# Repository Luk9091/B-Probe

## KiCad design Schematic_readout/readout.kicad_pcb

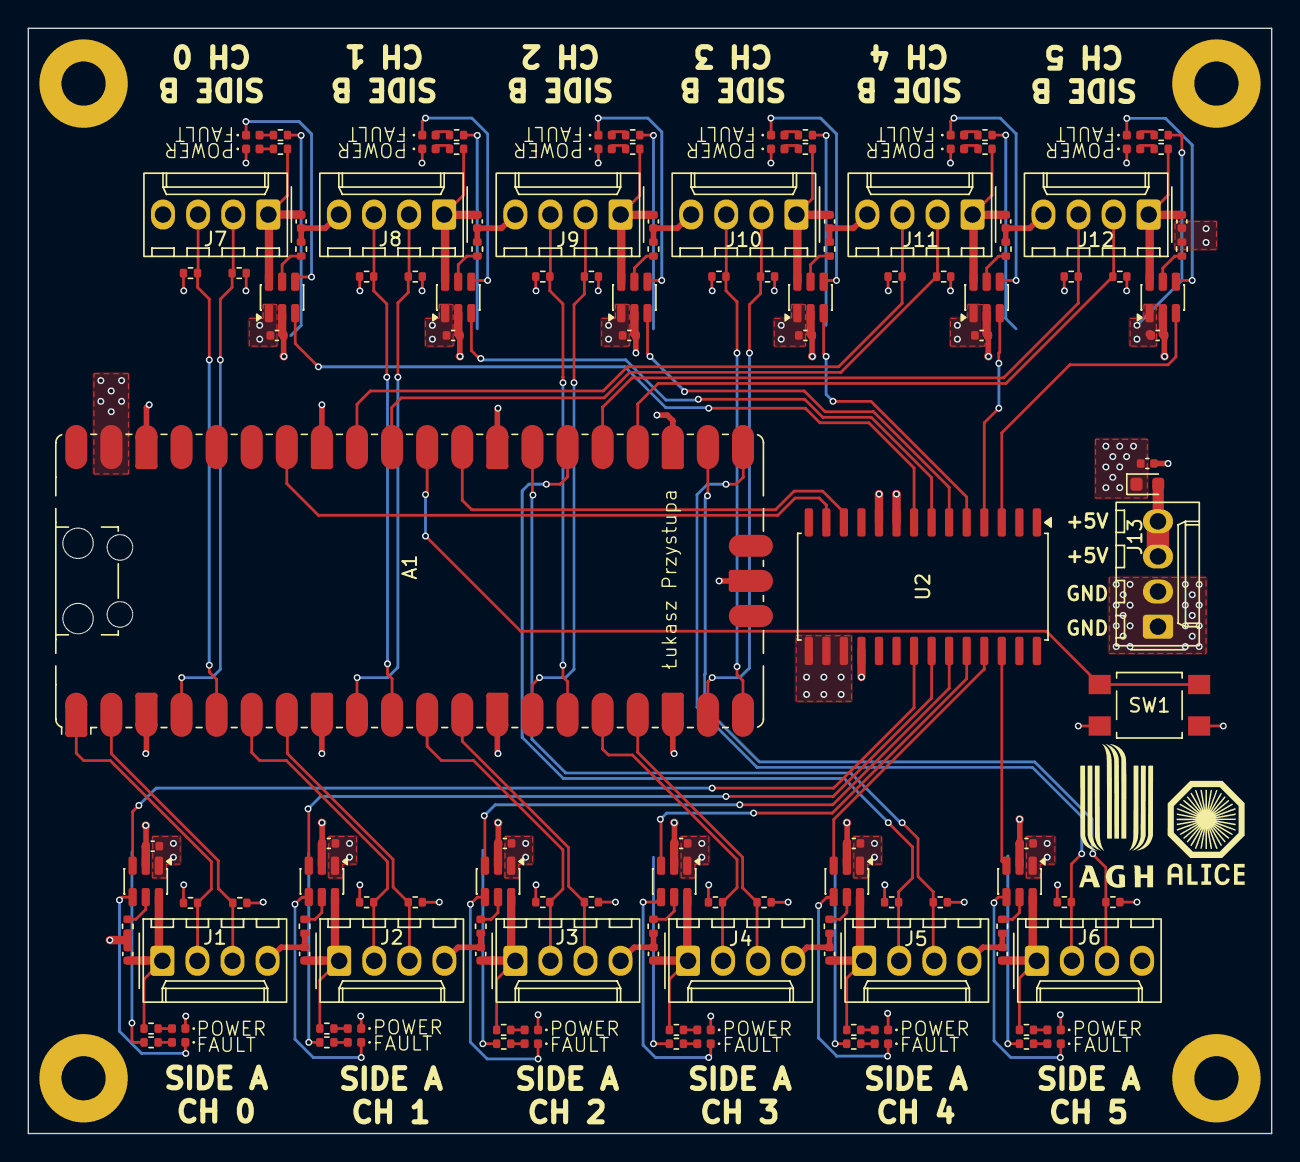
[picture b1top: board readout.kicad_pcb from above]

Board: 4 copper layers, 90.0 x 80.0 mm, 142 parts (0 on the bottom side), 103 nets.

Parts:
A1: RaspberryPi_Pico; RaspberryPi_Pico_SMD_HandSolder
C1, C2, C3, C4, C5, C6, C7, C8, C9, C10, C11, C12, C13, C14, C15, C16, C17, C18, C19, C20, C21, C22, C23, C24, C25: 1u; C_0402_1005Metric
D1, D3, D5, D7, D9, D11, D13, D15, D17, D19, D21, D23: FAULT LED; LED_0402_1005Metric
D2, D4, D6, D8, D10, D12, D14, D16, D18, D20, D22, D24: POWER LED; LED_0402_1005Metric
D25: NSR20F30NXT5G; D_0603_1608Metric
H1, H2, H3, H4: MountingHole_Pad; MountingHole_3.2mm_M3_Pad
J1, J2, J3, J4, J5, J6, J7, J8, J9, J10, J11, J12, J13: Conn_01x04; Molex_KK-254_AE-6410-04A_1x04_P2.54mm_Vertical
R1, R2, R6, R7, R11, R12, R16, R17, R21, R22, R26, R27, R31, R32, R36, R37, R41, R42, R46, R47, R51, R52, R56, R57: 8.6k; R_0402_1005Metric
R3, R8, R13, R18, R23, R28, R33, R38, R43, R48, R53, R58: 10k; R_0402_1005Metric
R4, R9, R14, R19, R24, R29, R34, R39, R44, R49, R54, R59: 82k; R_0402_1005Metric
R5, R10, R15, R20, R25, R30, R35, R40, R45, R50, R55, R60: 33k; R_0402_1005Metric
SW1: SW_Push; SW_SPST_TL3305B
U1, U3, U4, U5, U6, U7, U8, U9, U10, U11, U12, U13: AP22653QW6; SOT-23-6
U2: MCP23017x-x-SO; SOIC-28W_7.5x17.9mm_P1.27mm

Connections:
+3.3V: R1.1, R2.1, R6.1, R7.1, R11.1, R12.1, R16.1, R17.1, R21.1, R22.1, R26.1, R27.1, R31.1, R32.1, R36.1, R37.1, R41.1, R42.1, R46.1, R47.1, R51.1, R52.1, R56.1, R57.1, U2.9 (V_{DD}), U2.18 (~RESET)
+5V: A1.39 (VSYS), C2.1, C4.1, C6.1, C8.1, C10.1, C12.1, C14.1, C16.1, C18.1, C20.1, C22.1, C24.1, C25.1, D25.1 (K), R3.1, R8.1, R13.1, R18.1, R23.1, R28.1, R33.1, R38.1, R43.1, R48.1, R53.1, R58.1, U1.1 (IN), U3.1 (IN), U4.1 (IN), U5.1 (IN), U6.1 (IN), U7.1 (IN), U8.1 (IN), U9.1 (IN), U10.1 (IN), U11.1 (IN), U12.1 (IN), U13.1 (IN)
/Enable Ch0 0: U1.3 (EN/~EN), U2.21 (GPA0)
/Enable Ch0 1: U2.22 (GPA1), U3.3 (EN/~EN)
/Enable Ch0 2: U2.23 (GPA2), U4.3 (EN/~EN)
/Enable Ch0 3: U2.24 (GPA3), U5.3 (EN/~EN)
/Enable Ch0 4: U2.25 (GPA4), U6.3 (EN/~EN)
/Enable Ch0 5: U2.26 (GPA5), U7.3 (EN/~EN)
/Enable Ch1 0: U2.8 (GPB7), U8.3 (EN/~EN)
/Enable Ch1 1: U2.7 (GPB6), U9.3 (EN/~EN)
/Enable Ch1 2: U2.6 (GPB5), U10.3 (EN/~EN)
/Enable Ch1 3: U2.5 (GPB4), U11.3 (EN/~EN)
/Enable Ch1 4: U2.4 (GPB3), U12.3 (EN/~EN)
/Enable Ch1 5: U2.3 (GPB2), U13.3 (EN/~EN)
/I2C0_SCK_{0}: A1.2 (GPIO1), J1.3, R1.2
/I2C0_SCK_{1}: A1.7 (GPIO5), J2.3, R6.2
/I2C0_SCK_{2}: A1.12 (GPIO9), J3.3, R11.2
/I2C0_SCK_{3}: A1.17 (GPIO13), J4.3, R16.2
/I2C0_SCK_{4}: A1.27 (GPIO21), J5.3, R21.2
/I2C0_SCK_{5}: A1.22 (GPIO17), J6.3, R26.2
/I2C0_SDA_{0}: A1.1 (GPIO0), J1.2, R2.2
/I2C0_SDA_{1}: A1.6 (GPIO4), J2.2, R7.2
/I2C0_SDA_{2}: A1.11 (GPIO8), J3.2, R12.2
/I2C0_SDA_{3}: A1.16 (GPIO12), J4.2, R17.2
/I2C0_SDA_{4}: A1.26 (GPIO20), J5.2, R22.2
/I2C0_SDA_{5}: A1.21 (GPIO16), J6.2, R27.2
/I2C1_SCK_{0}: A1.5 (GPIO3), J7.3, R31.2
/I2C1_SCK_{1}: A1.10 (GPIO7), J8.3, R36.2
/I2C1_SCK_{2}: A1.15 (GPIO11), J9.3, R41.2
/I2C1_SCK_{3}: A1.20 (GPIO15), J10.3, R46.2
/I2C1_SCK_{4}: A1.32 (GPIO27_ADC1), J11.3, R51.2
/I2C1_SCK_{5}: A1.25 (GPIO19), J12.3, R56.2
/I2C1_SDA_{0}: A1.4 (GPIO2), J7.2, R32.2
/I2C1_SDA_{1}: A1.9 (GPIO6), J8.2, R37.2
/I2C1_SDA_{2}: A1.14 (GPIO10), J9.2, R42.2
/I2C1_SDA_{3}: A1.19 (GPIO14), J10.2, R47.2
/I2C1_SDA_{4}: A1.31 (GPIO26_ADC0), J11.2, R52.2
/I2C1_SDA_{5}: A1.24 (GPIO18), J12.2, R57.2
/Output I2C channel1/Inner 5V: C3.2, J2.1, R10.1, U3.6 (OUT)
/Output I2C channel2/Inner 5V: C5.2, J3.1, R15.1, U4.6 (OUT)
/Output I2C channel3/Inner 5V: C7.2, J4.1, R20.1, U5.6 (OUT)
/Output I2C channel4/Inner 5V: C9.2, J5.1, R25.1, U6.6 (OUT)
/Output I2C channel5/Inner 5V: C11.2, J6.1, R30.1, U7.6 (OUT)
/Output I2C channel6/Inner 5V: C13.2, J7.1, R35.1, U8.6 (OUT)
/Output I2C channel7/Inner 5V: C15.2, J8.1, R40.1, U9.6 (OUT)
/Output I2C channel8/Inner 5V: C17.2, J9.1, R45.1, U10.6 (OUT)
/Output I2C channel9/Inner 5V: C19.2, J10.1, R50.1, U11.6 (OUT)
/Output I2C channel10/Inner 5V: C21.2, J11.1, R55.1, U12.6 (OUT)
/Output I2C channel11/Inner 5V: C23.2, J12.1, R60.1, U13.6 (OUT)
/Output I2C channel/Inner 5V: C1.2, J1.1, R5.1, U1.6 (OUT)
/RUN: A1.30 (RUN), SW1.1
/SOFT_I2C_SCK: A1.29 (GPIO22), U2.12 (SCK)
/SOFT_I2C_SDA: A1.34 (GPIO28_ADC2), U2.13 (SDA)
GND: A1.3 (GND), A1.8 (GND), A1.13 (GND), A1.18 (GND), A1.23 (GND), A1.28 (GND), A1.33 (AGND), A1.38 (GND), A1.D2 (GND), C1.1, C2.2, C3.1, C4.2, C5.1, C6.2, C7.1, C8.2, C9.1, C10.2, C11.1, C12.2, C13.1, C14.2, C15.1, C16.2, C17.1, C18.2, C19.1, C20.2, C21.1, C22.2, C23.1, C24.2, C25.2, D2.1 (K), D4.1 (K), D6.1 (K), D8.1 (K), D10.1 (K), D12.1 (K), D14.1 (K), D16.1 (K), D18.1 (K), D20.1 (K), D22.1 (K), D24.1 (K), H1.1 (1_1), H2.1 (1_1), H3.1 (1_1), H4.1 (1_1), J1.4, J2.4, J3.4, J4.4, J5.4, J6.4, J7.4, J8.4, J9.4, J10.4, J11.4, J12.4, J13.1, J13.2, R4.2, R9.2, R14.2, R19.2, R24.2, R29.2, R34.2, R39.2, R44.2, R49.2, R54.2, R59.2, SW1.2, U1.2 (GND), U2.10 (V_{SS}), U2.15 (A0), U2.16 (A1), U2.17 (A2), U3.2 (GND), U4.2 (GND), U5.2 (GND), U6.2 (GND), U7.2 (GND), U8.2 (GND), U9.2 (GND), U10.2 (GND), U11.2 (GND), U12.2 (GND), U13.2 (GND)
unnamed: D1.2 (A), R3.2
unnamed: D1.1 (K), U1.4 (~FAULT)
unnamed: D2.2 (A), R5.2
unnamed: D3.2 (A), R8.2
unnamed: D3.1 (K), U3.4 (~FAULT)
unnamed: D4.2 (A), R10.2
unnamed: D5.2 (A), R13.2
unnamed: D5.1 (K), U4.4 (~FAULT)
unnamed: D6.2 (A), R15.2
unnamed: D7.2 (A), R18.2
unnamed: D7.1 (K), U5.4 (~FAULT)
unnamed: D8.2 (A), R20.2
unnamed: D9.2 (A), R23.2
unnamed: D9.1 (K), U6.4 (~FAULT)
unnamed: D10.2 (A), R25.2
unnamed: D11.2 (A), R28.2
unnamed: D11.1 (K), U7.4 (~FAULT)
unnamed: D12.2 (A), R30.2
unnamed: D13.2 (A), R33.2
unnamed: D13.1 (K), U8.4 (~FAULT)
unnamed: D14.2 (A), R35.2
unnamed: D15.2 (A), R38.2
unnamed: D15.1 (K), U9.4 (~FAULT)
unnamed: D16.2 (A), R40.2
unnamed: D17.2 (A), R43.2
unnamed: D17.1 (K), U10.4 (~FAULT)
unnamed: D18.2 (A), R45.2
unnamed: D19.2 (A), R48.2
unnamed: D19.1 (K), U11.4 (~FAULT)
unnamed: D20.2 (A), R50.2
unnamed: D21.2 (A), R53.2
unnamed: D21.1 (K), U12.4 (~FAULT)
unnamed: D22.2 (A), R55.2
unnamed: D23.2 (A), R58.2
unnamed: D23.1 (K), U13.4 (~FAULT)
unnamed: D24.2 (A), R60.2
unnamed: D25.2 (A), J13.3, J13.4
unnamed: R4.1, U1.5 (I_{LIM})
unnamed: R9.1, U3.5 (I_{LIM})
unnamed: R14.1, U4.5 (I_{LIM})
unnamed: R19.1, U5.5 (I_{LIM})
unnamed: R24.1, U6.5 (I_{LIM})
unnamed: R29.1, U7.5 (I_{LIM})
unnamed: R34.1, U8.5 (I_{LIM})
unnamed: R39.1, U9.5 (I_{LIM})
unnamed: R44.1, U10.5 (I_{LIM})
unnamed: R49.1, U11.5 (I_{LIM})
unnamed: R54.1, U12.5 (I_{LIM})
unnamed: R59.1, U13.5 (I_{LIM})

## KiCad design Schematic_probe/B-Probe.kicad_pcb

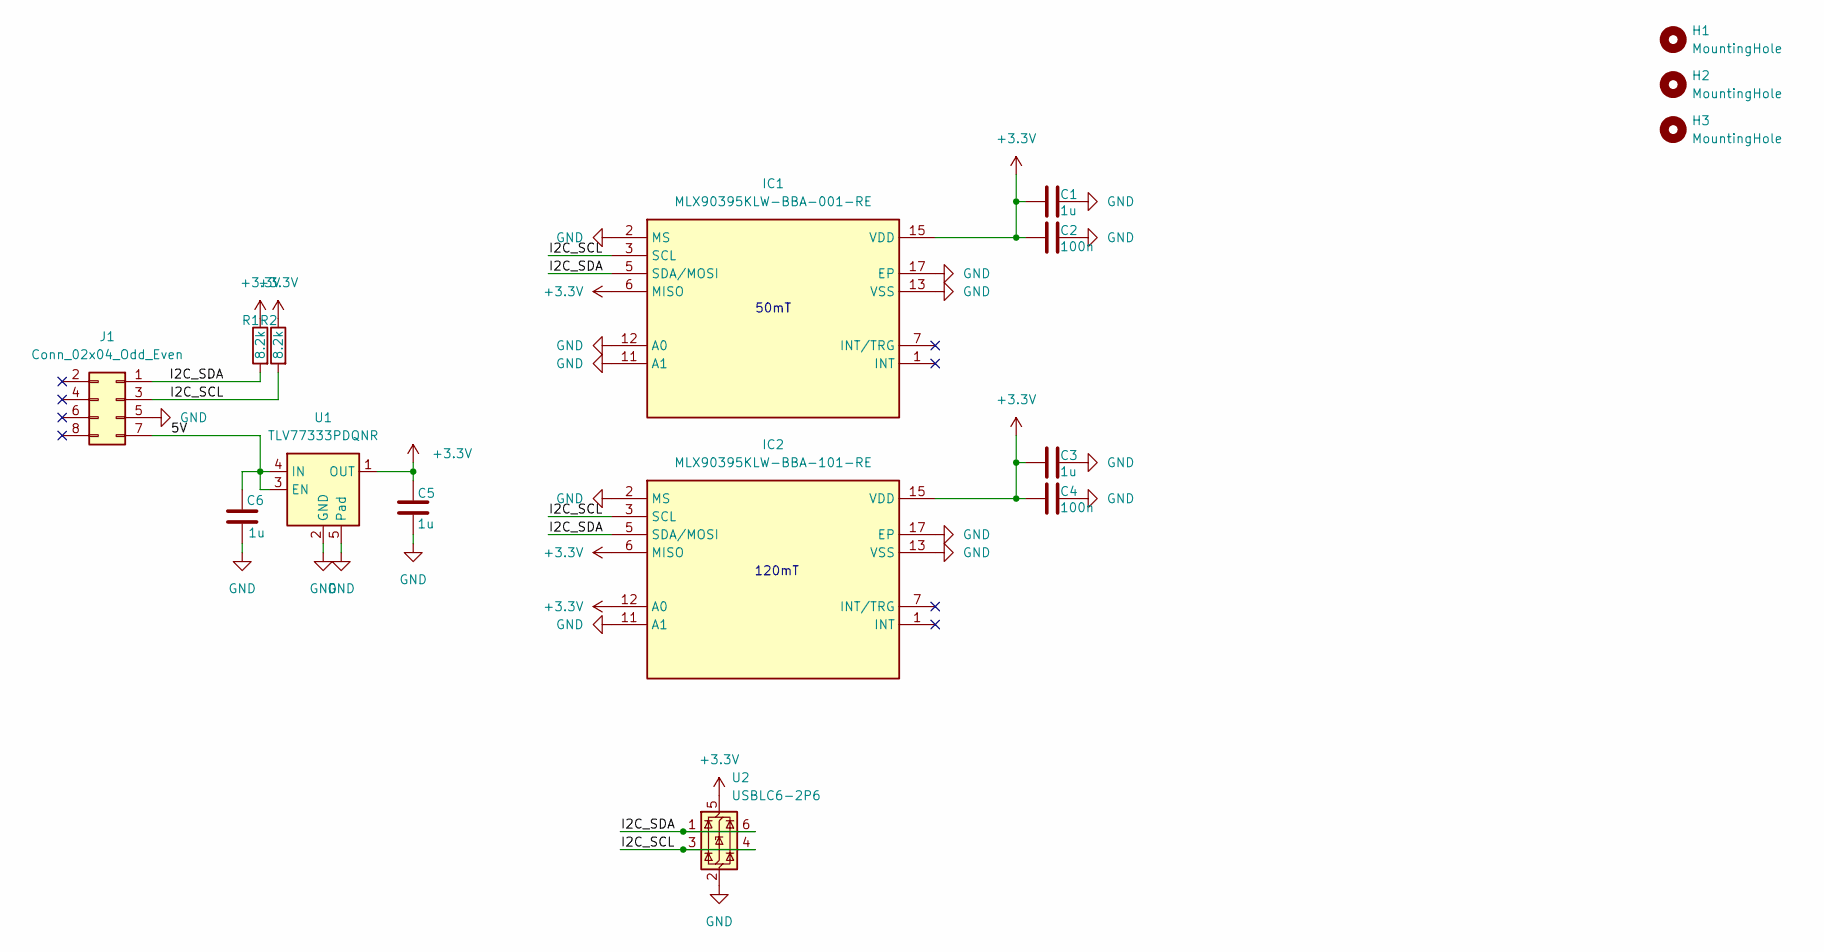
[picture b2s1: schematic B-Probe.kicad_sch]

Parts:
C1, C3, C5, C6: 1u; C_0201_0603Metric
C2, C4: 100n; C_0201_0603Metric
H1, H2, H3: MountingHole; MountingHole_2.2mm_M2
IC1: MLX90395KLW-BBA-001-RE; QFN50P300X300X100-17N-D; Mouser Part Number 482-90395KLWBBA001RE
IC2: MLX90395KLW-BBA-101-RE; QFN50P300X300X100-17N-D; Mouser Part Number 482-90395KLWBBA101RE
J1: Conn_02x04_Odd_Even; PinHeader_2x04_P1.27mm_Vertical
R1, R2: 8.2k; R_0201_0603Metric
U1: TLV77333PDQNR; Texas_X2SON-4_1x1mm_P0.65mm
U2: USBLC6-2P6; SOT-666

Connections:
+3.3V: C1.1, C2.1, C3.1, C4.1, C5.1, IC1.6 (MISO), IC1.15 (VDD), IC2.6 (MISO), IC2.12 (A0), IC2.15 (VDD), R1.1, R2.1, U1.1 (OUT), U2.5 (VBUS)
/5V: C6.1, J1.7, U1.3 (EN), U1.4 (IN)
/I2C_SCL: IC1.3 (SCL), IC2.3 (SCL), J1.3, R2.2, U2.3 (I/O2), U2.4 (I/O2)
/I2C_SDA: IC1.5 (SDA/MOSI), IC2.5 (SDA/MOSI), J1.1, R1.2, U2.1 (I/O1), U2.6 (I/O1)
GND: C1.2, C2.2, C3.2, C4.2, C5.2, C6.2, IC1.2 (MS), IC1.4 (NOT_USED_1), IC1.8 (NOT_USED_3), IC1.9 (NOT_USED_4), IC1.10 (NOT_USED_5), IC1.11 (A1), IC1.12 (A0), IC1.13 (VSS), IC1.14 (NOT_USED_6), IC1.16 (NOT_USED_7), IC1.17 (EP), IC2.2 (MS), IC2.4 (NOT_USED_1), IC2.8 (NOT_USED_3), IC2.9 (NOT_USED_4), IC2.10 (NOT_USED_5), IC2.11 (A1), IC2.13 (VSS), IC2.14 (NOT_USED_6), IC2.16 (NOT_USED_7), IC2.17 (EP), J1.5, U1.2 (GND), U1.5 (Pad), U2.2 (GND)

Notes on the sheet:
120mT
50mT

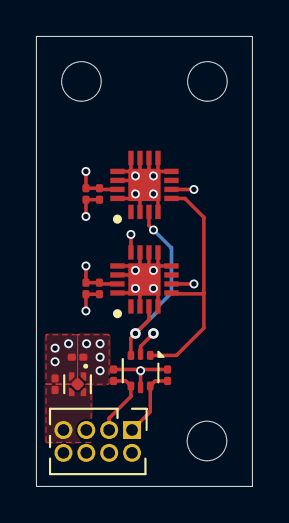
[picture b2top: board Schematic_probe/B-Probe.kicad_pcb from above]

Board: 4 copper layers, 12.0 x 25.0 mm, 16 parts (0 on the bottom side), 5 nets.

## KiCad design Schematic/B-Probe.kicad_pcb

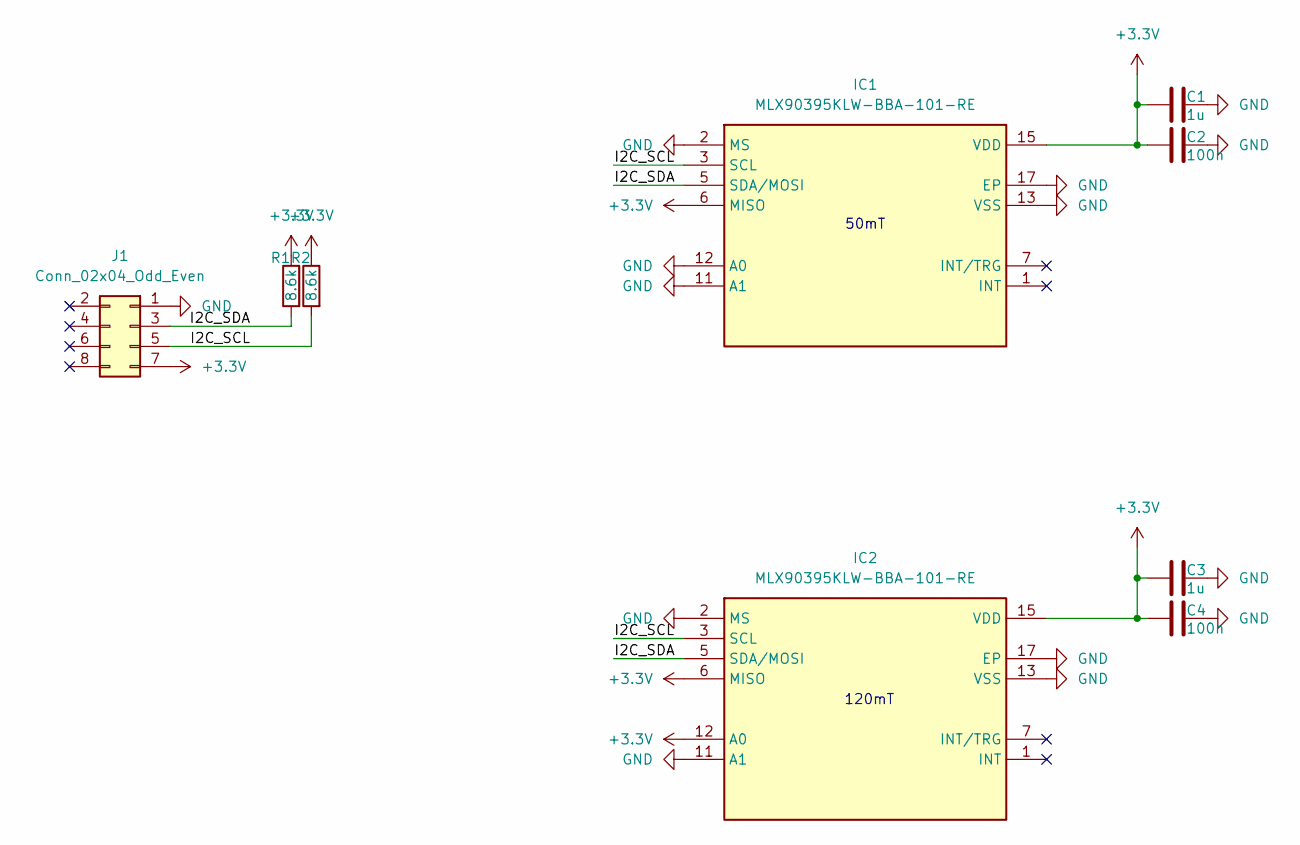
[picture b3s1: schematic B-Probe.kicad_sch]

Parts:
C1, C3: 1u; C_0201_0603Metric
C2, C4: 100n; C_0201_0603Metric
IC1, IC2: MLX90395KLW-BBA-101-RE; QFN50P300X300X100-17N-D; Mouser Part Number 482-90395KLWBBA101RE
J1: Conn_02x04_Odd_Even; PinHeader_2x04_P1.00mm_Vertical
R1, R2: 8.6k; R_0201_0603Metric

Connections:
+3.3V: C1.1, C2.1, C3.1, C4.1, IC1.6 (MISO), IC1.15 (VDD), IC2.6 (MISO), IC2.12 (A0), IC2.15 (VDD), J1.7, R1.1, R2.1
/I2C_SCL: IC1.3 (SCL), IC2.3 (SCL), J1.5, R2.2
/I2C_SDA: IC1.5 (SDA/MOSI), IC2.5 (SDA/MOSI), J1.3, R1.2
GND: C1.2, C2.2, C3.2, C4.2, IC1.2 (MS), IC1.4 (NOT_USED_1), IC1.8 (NOT_USED_3), IC1.9 (NOT_USED_4), IC1.10 (NOT_USED_5), IC1.11 (A1), IC1.12 (A0), IC1.13 (VSS), IC1.14 (NOT_USED_6), IC1.16 (NOT_USED_7), IC1.17 (EP), IC2.2 (MS), IC2.4 (NOT_USED_1), IC2.8 (NOT_USED_3), IC2.9 (NOT_USED_4), IC2.10 (NOT_USED_5), IC2.11 (A1), IC2.13 (VSS), IC2.14 (NOT_USED_6), IC2.16 (NOT_USED_7), IC2.17 (EP), J1.1

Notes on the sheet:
120mT
50mT

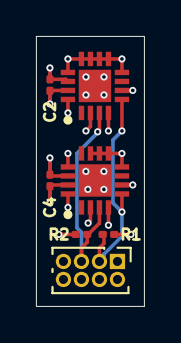
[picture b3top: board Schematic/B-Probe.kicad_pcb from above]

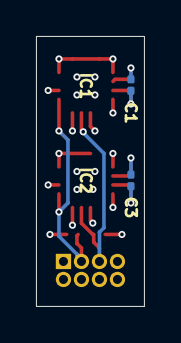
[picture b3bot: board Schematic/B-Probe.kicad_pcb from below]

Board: 4 copper layers, 6.0 x 15.0 mm, 9 parts (2 on the bottom side), 4 nets.
